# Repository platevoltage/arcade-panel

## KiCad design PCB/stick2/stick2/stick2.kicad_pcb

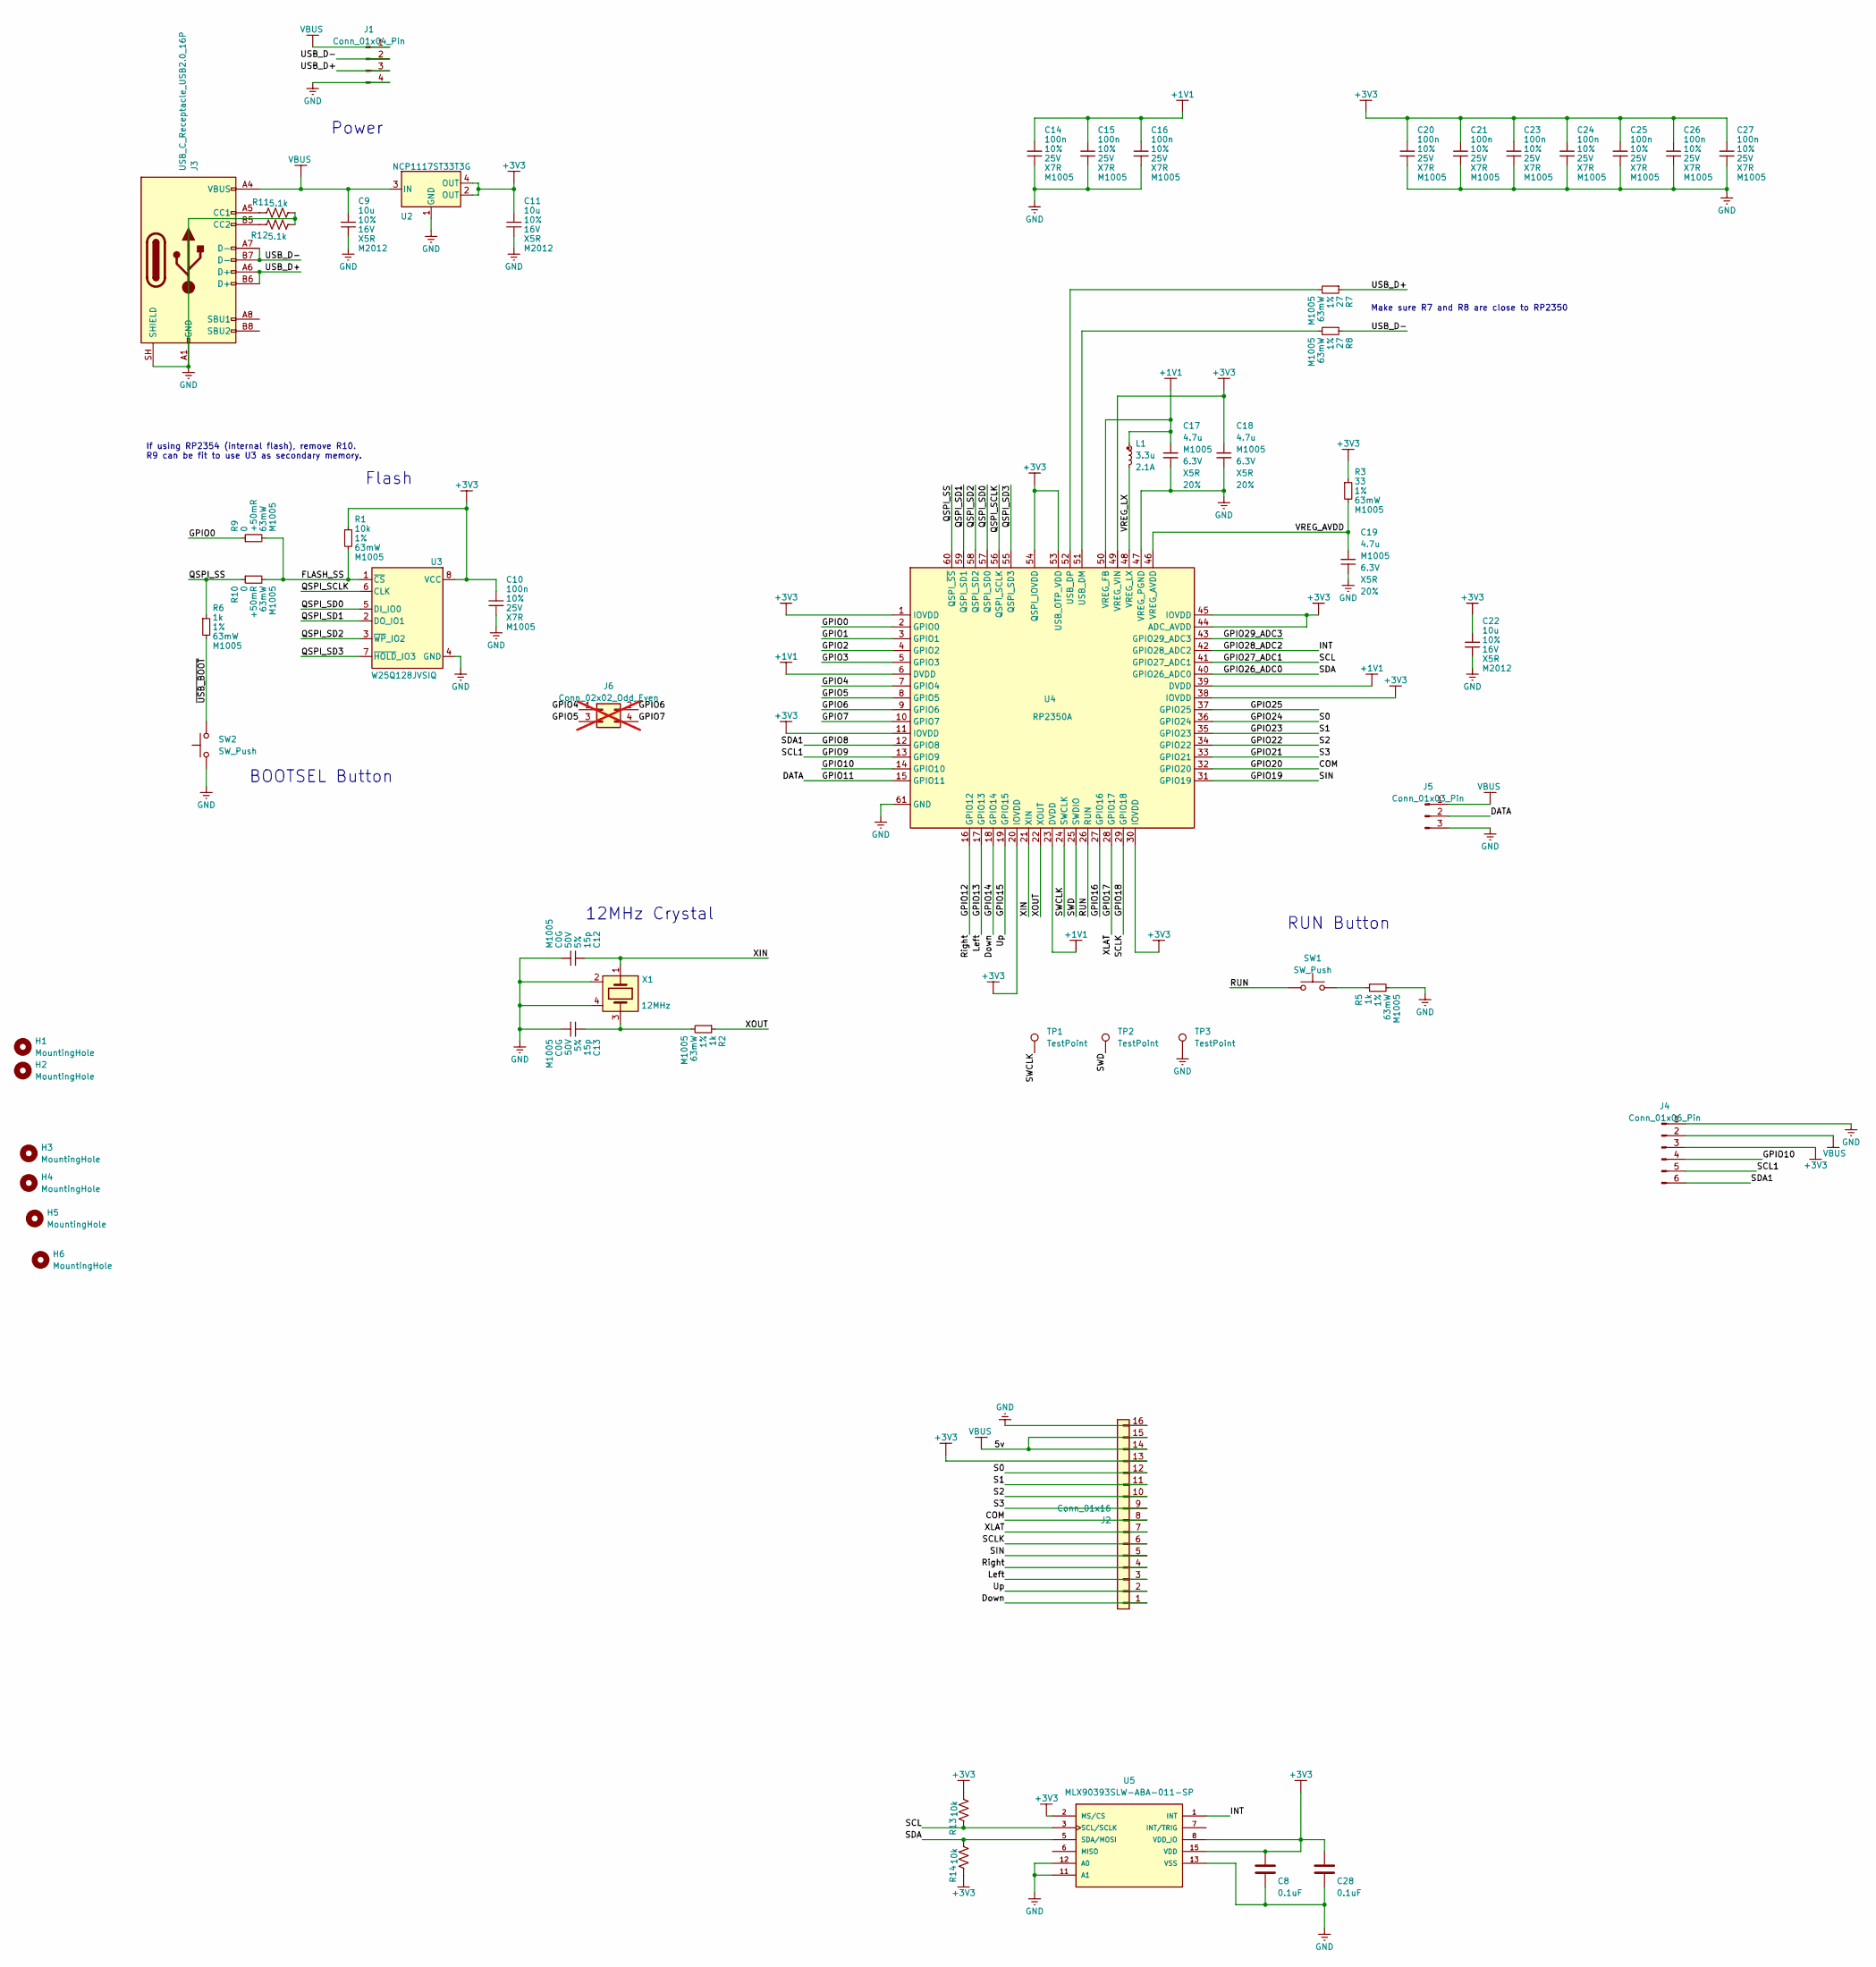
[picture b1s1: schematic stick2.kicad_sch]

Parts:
C8, C28: 0.1uF; C_0603_1608Metric_Pad1.08x0.95mm_HandSolder; LCSC C1525
C9, C11, C22: 10u; generic_capc2012x125; voltage 16V; tolerance 10%; part_uid RP-01GYSK-AVBE41; lcsc_pn C77075
C10, C14, C15, C16, C20, C21, C23, C24, C25, C26, C27: 100n; C_0603_1608Metric_Pad1.08x0.95mm_HandSolder; voltage 25V; tolerance 10%; part_uid RP-01BJ9Y-KRGF41; lcsc_pn C77014
C12, C13: 15p; C_0603_1608Metric_Pad1.08x0.95mm_HandSolder; voltage 50V; tolerance 5%; part_uid RP-01C89W-LLY9XV; lcsc_pn C77014
C17, C18: 4.7u; C_0603_1608Metric_Pad1.08x0.95mm_HandSolder; voltage 6.3V; tolerance 20%; part_uid RP-019A1P-0C2GHY; lcsc_pn C82453
C19: 4.7u; C_0603_1608Metric_Pad1.08x0.95mm_HandSolder; voltage 6.3V; tolerance 20%; part_uid RP-019A1P-0C2GHY; lcsc_pn C77014
H1, H2: MountingHole; MountingHole_6mm
H3, H4, H5, H6: MountingHole; MountingHole_2.2mm_M2
J1: Conn_01x04_Pin; PinHeader_1x04_P2.54mm_Horizontal
J2: Conn_01x16; PinSocket_1x16_P2.54mm_Horizontal
J3: USB_C_Receptacle_USB2.0_16P; USB_C_Receptacle_GCT_USB4110
J4: Conn_01x06_Pin; PinHeader_1x06_P2.54mm_Horizontal
J5: Conn_01x03_Pin; PinHeader_1x03_P2.54mm_Horizontal
J6: Conn_02x02_Odd_Even; PinHeader_2x02_P2.54mm_Vertical; not fitted
L1: 3.3u; abracon_aota-b201610s3r3-101-t; tolerance 20%; part_uid RP-01GY5D-2VC7WP; lcsc_pn C42411119
R1: 10k; R_0603_1608Metric_Pad0.98x0.95mm_HandSolder; tolerance 1%; voltage 50V; part_uid RP-019A1P-53DHSX; lcsc_pn C60490
R2, R5, R6: 1k; R_0603_1608Metric_Pad0.98x0.95mm_HandSolder; tolerance 1%; voltage 50V; part_uid RP-019A1P-4Z6ZWY; lcsc_pn C60490
R3: 33; R_0603_1608Metric_Pad0.98x0.95mm_HandSolder; tolerance 1%; voltage 50V; part_uid RP-019A1P-58PW9L; lcsc_pn C60490
R7, R8: 27; R_0603_1608Metric_Pad0.98x0.95mm_HandSolder; tolerance 1%; voltage 50V; part_uid RP-01C89V-LTEYC4; lcsc_pn C60490
R9, R10: 0; R_0603_1608Metric_Pad0.98x0.95mm_HandSolder; tolerance +50mR; voltage 50V; part_uid RP-019A1P-4Y4V63; lcsc_pn C60490
R11, R12: 5.1k; R_0603_1608Metric_Pad0.98x0.95mm_HandSolder; MFR.Part # RC0603JR-075K1L; JLCPCB Part # C14677
R13, R14: 10k; R_0603_1608Metric_Pad0.98x0.95mm_HandSolder; MFR.Part # RC0603JR-075K1L; JLCPCB Part # C14677
SW1, SW2: SW_Push; SW_SPST_B3U-3000P; Manufacturer Part Numbe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 PTS636 SKG25J SMTR LFS; JLCPCB Part # C2689642
TP1, TP2, TP3: TestPoint; TestPoint_Pad_D2.0mm
U2: NCP1117ST33T3G; onsemi_ncp1117st33t3g; voltage 3.3V; part_uid RP-01JWD9-7JRX6J; lcsc_pn C26537
U3: W25Q128JVSIQ; generic_soic127p790x195-8; voltage 2.7-3.6V; part_uid RP-01JWD4-F1H4N9; lcsc_pn C97521
U4: RP2350A; rpi_rp2350a_vias; part_uid RP-01HA9H-9K5E8T; lcsc_pn C42411118
U5: MLX90393SLW-ABA-011-SP; QFN50P300X300X100-17N; PARTREV 010; LCSC C5371633
X1: 12MHz; generic_xtalcc320x250x80-4; tolerance 30ppm; part_uid RP-01G8X7-GS352B; lcsc_pn C20625731

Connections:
+1V1: C14.1, C15.1, C16.1, C17.1, L1.1, U4.6 (DVDD), U4.23 (DVDD), U4.39 (DVDD), U4.50 (VREG_FB)
+3V3: C8.1, C10.1, C11.1, C18.1, C20.1, C21.1, C22.1, C23.1, C24.1, C25.1, C26.1, C27.1, C28.1, J2.13, J4.3, R1.1, R3.1, R13.2, R14.1, U2.2 (OUT), U2.4 (OUT), U3.8 (VCC), U4.1 (IOVDD), U4.11 (IOVDD), U4.20 (IOVDD), U4.30 (IOVDD), U4.38 (IOVDD), U4.44 (ADC_AVDD), U4.45 (IOVDD), U4.49 (VREG_VIN), U4.53 (USB_OTP_VDD), U4.54 (QSPI_IOVDD), U5.2 (MS/CS), U5.8 (VDD_IO), U5.15 (VDD)
/COM: J2.8, U4.32 (GPIO20)
/DATA: J5.2, U4.15 (GPIO11)
/Down: J2.1, U4.18 (GPIO14)
/FLASH_SS: R1.2, R9.2, R10.2, U3.1 (~CS)
/GPIO0: R9.1, U4.2 (GPIO0)
/GPIO1: U4.3 (GPIO1)
/GPIO2: U4.4 (GPIO2)
/GPIO3: U4.5 (GPIO3)
/GPIO4: J6.1, U4.7 (GPIO4)
/GPIO5: J6.3, U4.8 (GPIO5)
/GPIO6: J6.2, U4.9 (GPIO6)
/GPIO7: J6.4, U4.10 (GPIO7)
/GPIO8: J4.6, U4.12 (GPIO8)
/GPIO9: J4.5, U4.13 (GPIO9)
/GPIO10: J4.4, U4.14 (GPIO10)
/GPIO12: J2.4, U4.16 (GPIO12)
/GPIO13: J2.3, U4.17 (GPIO13)
/GPIO15: J2.2, U4.19 (GPIO15)
/GPIO16: U4.27 (GPIO16)
/GPIO17: J2.7, U4.28 (GPIO17)
/GPIO18: J2.6, U4.29 (GPIO18)
/GPIO19: J2.5, U4.31 (GPIO19)
/GPIO21: J2.9, U4.33 (GPIO21)
/GPIO22: J2.10, U4.34 (GPIO22)
/GPIO23: J2.11, U4.35 (GPIO23)
/GPIO24: J2.12, U4.36 (GPIO24)
/GPIO25: U4.37 (GPIO25)
/GPIO26_ADC0: R14.2, U4.40 (GPIO26_ADC0), U5.5 (SDA/MOSI)
/GPIO27_ADC1: R13.1, U4.41 (GPIO27_ADC1), U5.3 (SCL/SCLK)
/GPIO28_ADC2: U4.42 (GPIO28_ADC2), U5.1 (INT)
/GPIO29_ADC3: U4.43 (GPIO29_ADC3)
/QSPI_SCLK: U3.6 (CLK), U4.56 (QSPI_SCLK)
/QSPI_SD0: U3.5 (DI_IO0), U4.57 (QSPI_SD0)
/QSPI_SD1: U3.2 (DO_IO1), U4.59 (QSPI_SD1)
/QSPI_SD2: U3.3 (~WP_IO2), U4.58 (QSPI_SD2)
/QSPI_SD3: U3.7 (~HOLD_IO3), U4.55 (QSPI_SD3)
/QSPI_SS: R6.1, R10.1, U4.60 (QSPI_~SS)
/RUN: SW1.1, U4.26 (RUN)
/SWCLK: TP1.1 (1_1), U4.24 (SWCLK)
/SWD: TP2.1 (1_1), U4.25 (SWDIO)
/USB_D+: J1.3, J3.A6 (D+), J3.B6 (D+), R7.1
/USB_D-: J1.2, J3.A7 (D-), J3.B7 (D-), R8.1
/VREG_AVDD: C19.1, R3.2, U4.46 (VREG_AVDD)
/VREG_LX: L1.2, U4.48 (VREG_LX)
/XIN: C12.1, U4.21 (XIN), X1.1
/XOUT: R2.1, U4.22 (XOUT)
/~USB_BOOT: R6.2, SW2.2
unnamed: C13.1, R2.2, X1.3
unnamed: J3.A5 (CC1), R11.1
unnamed: J3.B5 (CC2), R12.1
unnamed: R5.1, SW1.2
unnamed: R8.2, U4.51 (USB_DM)
unnamed: R7.2, U4.52 (USB_DP)
VBUS: C9.1, J1.1, J2.14, J2.15, J3.A4 (VBUS), J3.A9 (VBUS), J3.B4 (VBUS), J3.B9 (VBUS), J4.2, J5.1, U2.3 (IN)

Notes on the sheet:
Make sure R7 and R8 are close to RP2350
12MHz Crystal
Power
BOOTSEL Button
If using RP2354 (internal flash), remove R10. R9 can be fit to use U3 as secondary memory.
RUN Button
Flash

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
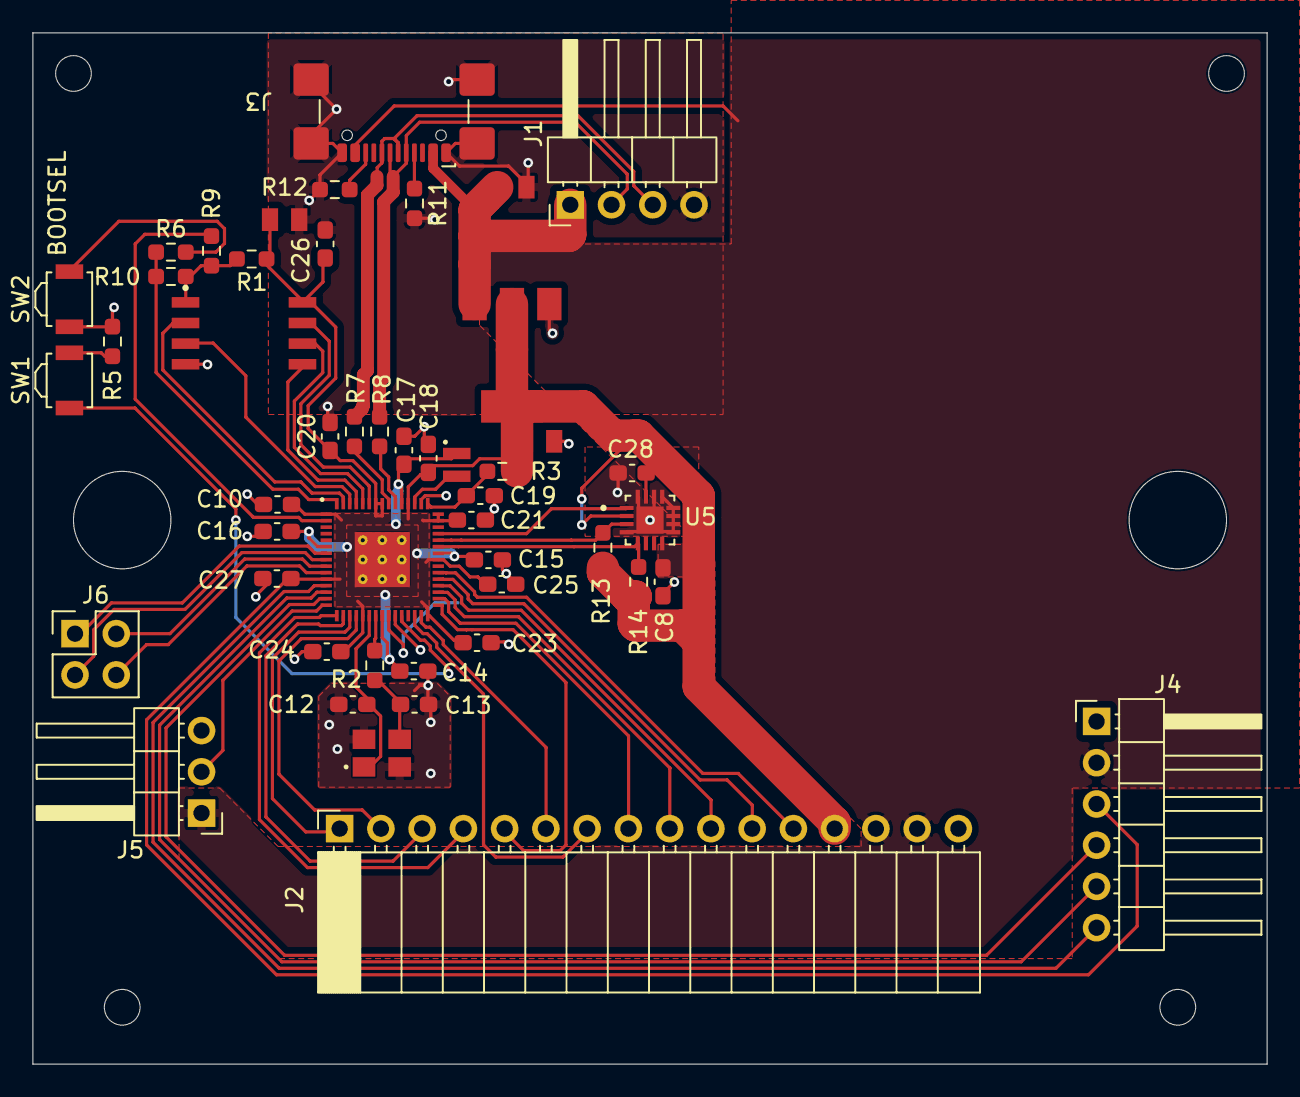
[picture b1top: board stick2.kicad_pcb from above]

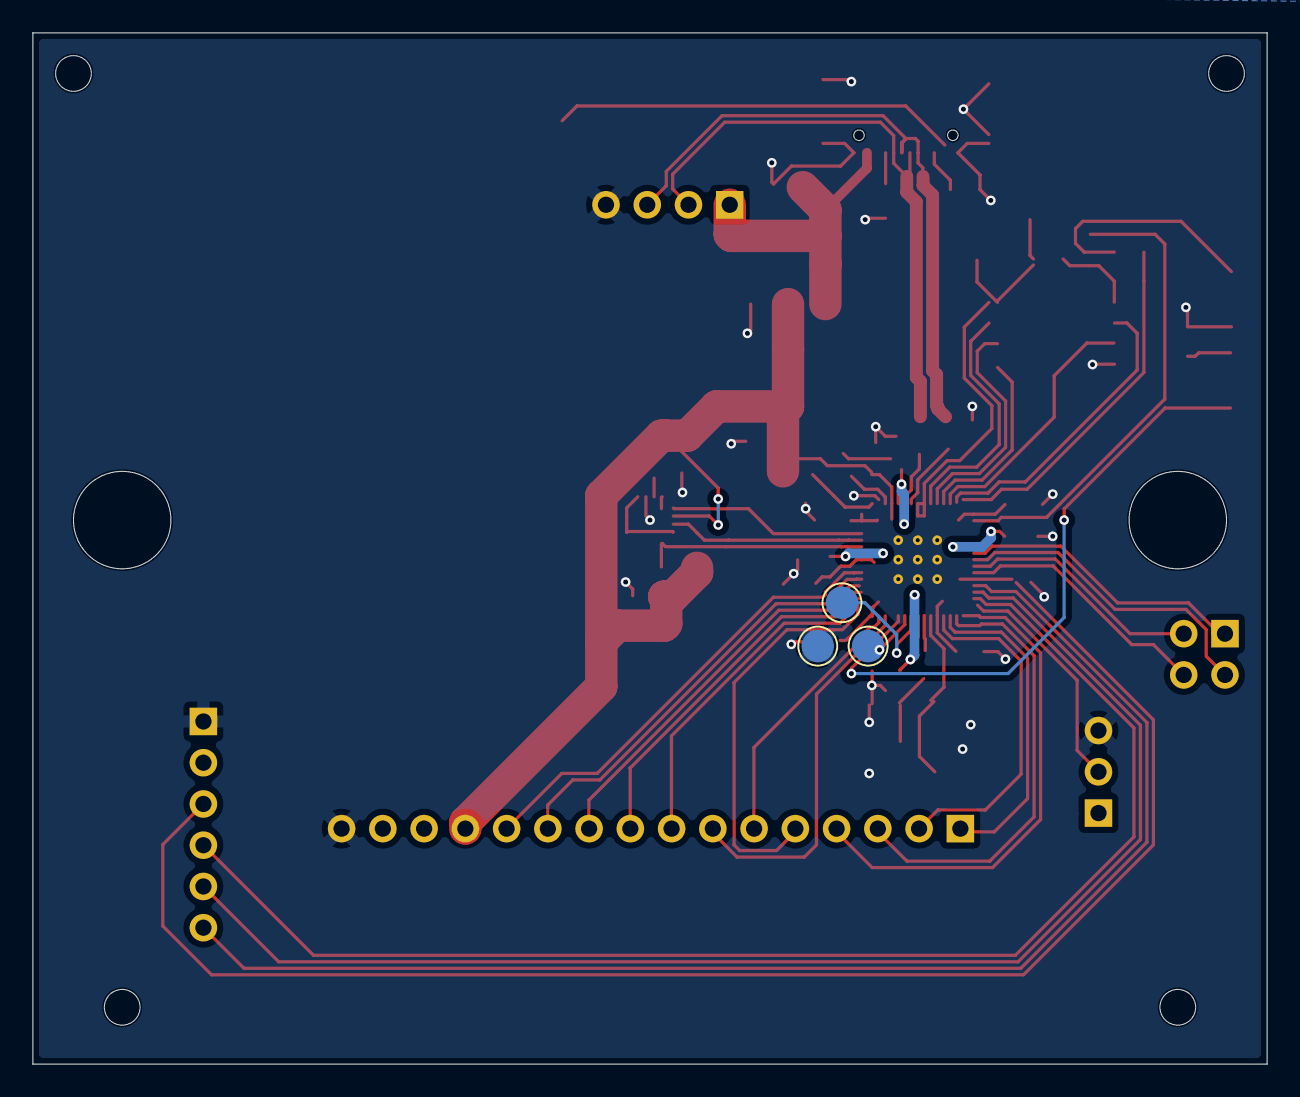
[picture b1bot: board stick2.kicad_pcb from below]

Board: 2 copper layers, 76.0 x 63.5 mm, 57 parts (3 on the bottom side), 51 nets.

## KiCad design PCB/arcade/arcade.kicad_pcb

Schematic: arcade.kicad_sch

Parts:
C1, C2: 10uf; C_0603_1608Metric_Pad1.08x0.95mm_HandSolder; MFR.Part # CC0603MRX5R5BB106; JLCPCB Part # C109454
C6: 100nf; C_0603_1608Metric_Pad1.08x0.95mm_HandSolder; MFR.Part # CC0603KRX7R0BB104; JLCPCB Part # C113803
C15, C17, C18, C19, C20, C21, C22, C23, C24: 100nf; C_0603_1608Metric_Pad1.08x0.95mm_HandSolder; MFR.Part # CC0603JRNPO9BN220; JLCPCB Part # C105620
C16: 2.2uf; C_0603_1608Metric_Pad1.08x0.95mm_HandSolder; MFR.Part # CC0603JRNPO9BN220; JLCPCB Part # C105620
D1: SK6812MINI-E; LED_SK6812MINI_PLCC4_3.5x3.5mm_P1.75mm
H1, H2, H3, H4: MountingHole; MountingHole_2.5mm_Pad_TopBottom
J1: USB_C_Receptacle_USB2.0_16P; USB_C_Receptacle_GCT_USB4110
J2: Conn_02x03_Odd_Even; PinHeader_2x03_P2.54mm_Horizontal
J3: Conn_02x06_Odd_Even; PinHeader_2x06_P2.54mm_Horizontal
J4: Screw_Terminal_01x02; TerminalBlock_Phoenix_MKDS-3-2-5.08_1x02_P5.08mm_Horizontal
J5, J7: Screw_Terminal_01x12; TerminalBlock_Phoenix_MPT-0,5-12-2.54_1x12_P2.54mm_Horizont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
J6: Screw_Terminal_01x08; TerminalBlock_Phoenix_MPT-0,5-8-2.54_1x08_P2.54mm_Horizontal
J8: Conn_01x02_Pin; PinHeader_1x02_P2.54mm_Vertical
J9: Conn_01x06_Pin; PinHeader_1x06_P2.54mm_Vertical
J10: USB3_A_Stacked; USB3_A_Molex_48406-0001_Horizontal_Stacked
J11: USB_A_Stacked; USB_A_CUI_UJ2-ADH-TH_Horizontal_Stacked
J13: HDMI_A_1.4; HDMI_A_Amphenol_10029449-x01xLF_Horizontal
J15, J16: Conn_02x24_Odd_Even; PinHeader_2x24_P2.54mm_Horizontal
Module1: ComputeModule5-CM5; Raspberry-Pi-5-Compute-Module
R4, R5, R10: 5.1k; R_0603_1608Metric_Pad0.98x0.95mm_HandSolder; MFR.Part # RC0603JR-075K1L; JLCPCB Part # C14677
R11, R12: 27; R_0603_1608Metric_Pad0.98x0.95mm_HandSolder; MFR.Part # RC0603JR-075K1L; JLCPCB Part # C14677
U1: RP2040; QFN-56-1EP_7x7mm_P0.4mm_EP3.2x3.2mm
U2, U3, U4: TLC5947RHB; QFN-32-1EP_5x5mm_P0.5mm_EP3.45x3.45mm
U5: ME6211C33M5; SOT-23-5; MFR.Part # ME6211C33M5G-N; JLCPCB Part # C82942
U6, U7: CD74HC4067M; SSOP-24_5.3x8.2mm_P0.65mm
U8: W25Q16JVSS; SOIC-8_5.3x5.3mm_P1.27mm
U9: TS3USB221ARSERG4; RSE10
U10: TCA9548AMRGER; Texas_RGE0024C_VQFN-24-1EP_4x4mm_P0.5mm_EP2.1x2.1mm
Y3: Crystal_GND24; Crystal_SMD_2520-4Pin_2.5x2.0mm; MFR.Part # XYDBPCNANF-12MHZ; JLCPCB Part # C521567

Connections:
/3.3v: C2.1, C6.1, C15.1, C16.1, C17.2, C18.2, C19.2, C20.2, C21.2, C22.2, J3.9, J3.10, U1.1 (IOVDD), U1.10 (IOVDD), U1.22 (IOVDD), U1.33 (IOVDD), U1.42 (IOVDD), U1.49 (IOVDD), U5.5 (V_{OUT}), U6.24 (VCC), U7.24 (VCC), U8.8 (VCC)
/CS1: J3.1
/CS2: J3.2
/D1+: R12.2
/D1-: R11.2
/DU+: J1.A6 (D+), J1.B6 (D+)
/DU-: J1.A7 (D-), J1.B7 (D-)
/EXT_5V: J2.5, J2.6, J4.2, J8.1, J15.7, J15.8, J15.15, J15.16, J15.23, J15.24, J15.31, J15.32, J15.39, J15.40, J15.47, J15.48, J16.7, J16.8, J16.15, J16.16, J16.23, J16.24, J16.31, J16.32, J16.39, J16.40, J16.47, J16.48, U2.28 (VCC), U3.28 (VCC), U4.28 (VCC)
/GND: C1.2, C2.2, C6.2, C15.2, C16.2, C17.1, C18.1, C19.1, C20.1, C21.1, C22.1, C23.1, C24.2, D1.3 (VDD), J1.A1 (GND), J1.A12 (GND), J1.B1 (GND), J1.B12 (GND), J1.S1 (SHIELD), J2.1, J2.2, J3.11, J3.12, J4.1, J9.6, R4.2, R5.2, U1.57 (GND), U2.29 (GND), U2.33 (PowerPAD), U3.29 (GND), U3.33 (PowerPAD), U4.29 (GND), U4.33 (PowerPAD), U5.2 (V_{SS}), U6.12 (GND), U7.12 (GND), U8.4 (GND), Y3.2, Y3.4
/IO14: D1.2 (DIN)
/IO38: J2.4
/IO40: U2.26 (XLAT), U3.26 (XLAT), U4.26 (XLAT)
/IO41: U2.31 (SCLK), U3.31 (SCLK), U4.31 (SCLK)
/IO42: U2.32 (SIN)
/MISO: J3.3, J3.4
/MOSI: J3.5, J3.6
/PD0: U6.10 (S0), U7.10 (S0)
/PD1: U6.11 (S1), U7.11 (S1)
/PD4: U6.14 (S2), U7.14 (S2)
/PD5: U6.15 (~E)
/PD6: U6.13 (S3), U7.13 (S3)
/PD7: U7.15 (~E)
/QSPI_SCLK: U1.52 (QSPI_SCLK), U8.6 (CLK)
/QSPI_SD0: U1.53 (QSPI_SD0), U8.5 (DI/IO_{0})
/QSPI_SD1: U1.55 (QSPI_SD1), U8.2 (DO/IO_{1})
/QSPI_SD2: U1.54 (QSPI_SD2), U8.3 (~WP/IO_{2})
/QSPI_SD3: U1.51 (QSPI_SD3), U8.7 (~HOLD/~RESET/IO_{3})
/QSPI_SS: U1.56 (~QSPI_SS), U8.1 (~CS)
/RX0: J9.2, U1.17 (GPIO14)
/SCK: J3.7, J3.8
/TX0: J9.3, U1.16 (GPIO13)
/VBUS: C1.1, D1.1 (VSS), J1.A4 (VBUS), J1.A9 (VBUS), J1.B4 (VBUS), J1.B9 (VBUS), J8.2, J9.4, U5.1 (V_{IN}), U5.3 (CE)
/XIN: C24.1, U1.20 (XIN), Y3.1
/XOUT: R10.2, U1.21 (XOUT)
unnamed: C23.2, R10.1, Y3.3
unnamed: J1.A5 (CC1), R4.1
unnamed: J1.B5 (CC2), R5.1
unnamed: J5.1, U6.20 (I11)
unnamed: J5.2, U6.21 (I10)
unnamed: J5.3, U6.22 (I9)
unnamed: J5.4, U6.23 (I8)
unnamed: J5.5, U6.2 (I7)
unnamed: J5.6, U6.3 (I6)
unnamed: J5.7, U6.4 (I5)
unnamed: J5.8, U6.5 (I4)
unnamed: J5.9, U6.6 (I3)
unnamed: J5.10, U6.7 (I2)
unnamed: J5.11, U6.8 (I1)
unnamed: J5.12, U6.9 (I0)
unnamed: J6.1, U6.19 (I12)
unnamed: J6.2, U6.18 (I13)
unnamed: J6.3, U6.17 (I14)
unnamed: J6.4, U6.16 (I15)
unnamed: J6.5, U7.9 (I0)
unnamed: J6.6, U7.8 (I1)
unnamed: J6.7, U7.7 (I2)
unnamed: J6.8, U7.6 (I3)
unnamed: J7.1, U7.5 (I4)
unnamed: J7.2, U7.4 (I5)
unnamed: J7.3, U7.3 (I6)
unnamed: J7.4, U7.2 (I7)
unnamed: J7.5, U7.23 (I8)
unnamed: J7.6, U7.22 (I9)
unnamed: J7.7, U7.21 (I10)
unnamed: J7.8, U7.20 (I11)
unnamed: J7.9, U7.19 (I12)
unnamed: J7.10, U7.18 (I13)
unnamed: J7.11, U7.17 (I14)
unnamed: J7.12, U7.16 (I15)
unnamed: J15.1, U2.24 (OUT23)
unnamed: J15.2, U3.13 (OUT12)
unnamed: J15.3, U2.23 (OUT22)
unnamed: J15.4, U3.14 (OUT13)
unnamed: J15.5, U2.22 (OUT21)
unnamed: J15.6, U3.15 (OUT14)
unnamed: J15.9, U2.21 (OUT20)
unnamed: J15.10, U3.16 (OUT15)
unnamed: J15.11, U2.20 (OUT19)
unnamed: J15.12, U3.17 (OUT16)
unnamed: J15.13, U2.19 (OUT18)
unnamed: J15.14, U3.18 (OUT17)
unnamed: J15.17, U2.18 (OUT17)
unnamed: J15.18, U3.19 (OUT18)
unnamed: J15.19, U2.17 (OUT16)
unnamed: J15.20, U3.20 (OUT19)
unnamed: J15.21, U2.16 (OUT15)
unnamed: J15.22, U3.21 (OUT20)
unnamed: J15.25, U2.15 (OUT14)
unnamed: J15.26, U3.22 (OUT21)
unnamed: J15.27, U2.14 (OUT13)
unnamed: J15.28, U3.23 (OUT22)
unnamed: J15.29, U2.13 (OUT12)
unnamed: J15.30, U3.24 (OUT23)
unnamed: J15.33, U2.12 (OUT11)
unnamed: J15.34, U2.1 (OUT0)
unnamed: J15.35, U2.11 (OUT10)
unnamed: J15.36, U2.2 (OUT1)
unnamed: J15.37, U2.10 (OUT9)
unnamed: J15.38, U2.3 (OUT2)
unnamed: J15.41, U2.9 (OUT8)
unnamed: J15.42, U2.4 (OUT3)
unnamed: J15.43, U2.8 (OUT7)
unnamed: J15.44, U2.5 (OUT4)
unnamed: J15.45, U2.7 (OUT6)
unnamed: J15.46, U2.6 (OUT5)
unnamed: J16.1, U4.18 (OUT17)
unnamed: J16.2, U4.19 (OUT18)
unnamed: J16.3, U4.17 (OUT16)
unnamed: J16.4, U4.20 (OUT19)
unnamed: J16.5, U4.16 (OUT15)
unnamed: J16.6, U4.21 (OUT20)
unnamed: J16.9, U4.15 (OUT14)
unnamed: J16.10, U4.22 (OUT21)
unnamed: J16.11, U4.14 (OUT13)
unnamed: J16.12, U4.23 (OUT22)
unnamed: J16.13, U4.13 (OUT12)
unnamed: J16.14, U4.24 (OUT23)
unnamed: J16.17, U4.12 (OUT11)
unnamed: J16.18, U3.1 (OUT0)
unnamed: J16.19, U4.11 (OUT10)
unnamed: J16.20, U3.2 (OUT1)
unnamed: J16.21, U4.10 (OUT9)
unnamed: J16.22, U3.3 (OUT2)
unnamed: J16.25, U4.9 (OUT8)
unnamed: J16.26, U3.4 (OUT3)
unnamed: J16.27, U4.8 (OUT7)
unnamed: J16.28, U3.5 (OUT4)
unnamed: J16.29, U4.7 (OUT6)
unnamed: J16.30, U3.6 (OUT5)
unnamed: J16.33, U4.6 (OUT5)
unnamed: J16.34, U3.7 (OUT6)
unnamed: J16.35, U4.5 (OUT4)
unnamed: J16.36, U3.8 (OUT7)
unnamed: J16.37, U4.4 (OUT3)
unnamed: J16.38, U3.9 (OUT8)
unnamed: J16.41, U4.3 (OUT2)
unnamed: J16.42, U3.10 (OUT9)
unnamed: J16.43, U4.2 (OUT1)
unnamed: J16.44, U3.11 (OUT10)
unnamed: J16.45, U4.1 (OUT0)
unnamed: J16.46, U3.12 (OUT11)
unnamed: U1.23 (DVDD), U1.50 (DVDD)
unnamed: R11.1, U1.46 (USB_DM)
unnamed: R12.1, U1.47 (USB_DP)
unnamed: U2.25 (SOUT), U3.32 (SIN)
unnamed: U3.25 (SOUT), U4.32 (SIN)

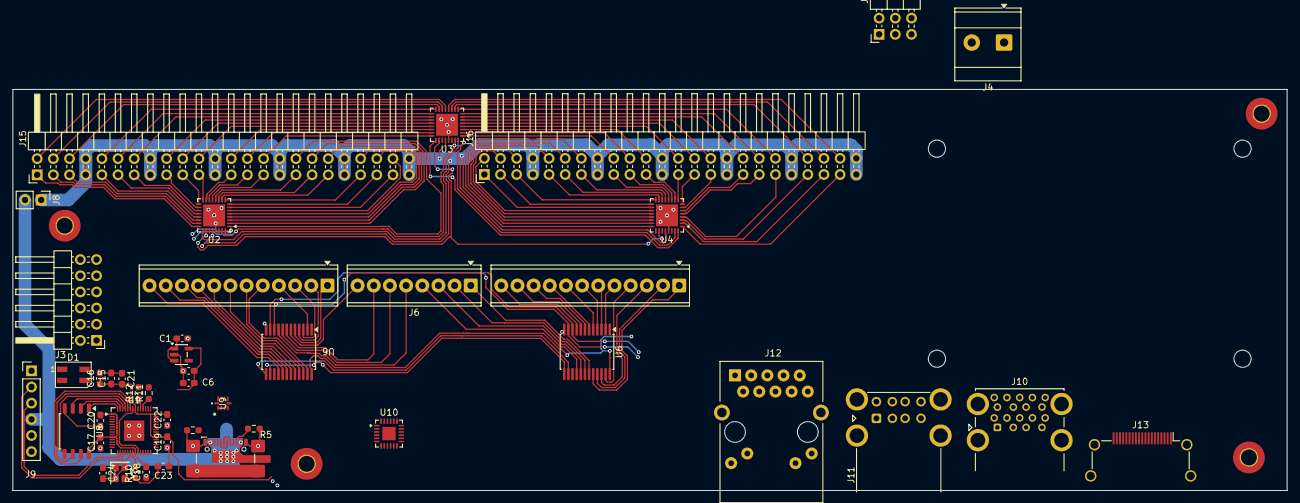
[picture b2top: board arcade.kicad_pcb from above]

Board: 4 copper layers, 200.1 x 63.0 mm, 50 parts (1 on the bottom side), 137 nets.

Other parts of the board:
J12: RJ45_RB1-125B8G1A; RJ45_UDE_RB1-125B8G1A

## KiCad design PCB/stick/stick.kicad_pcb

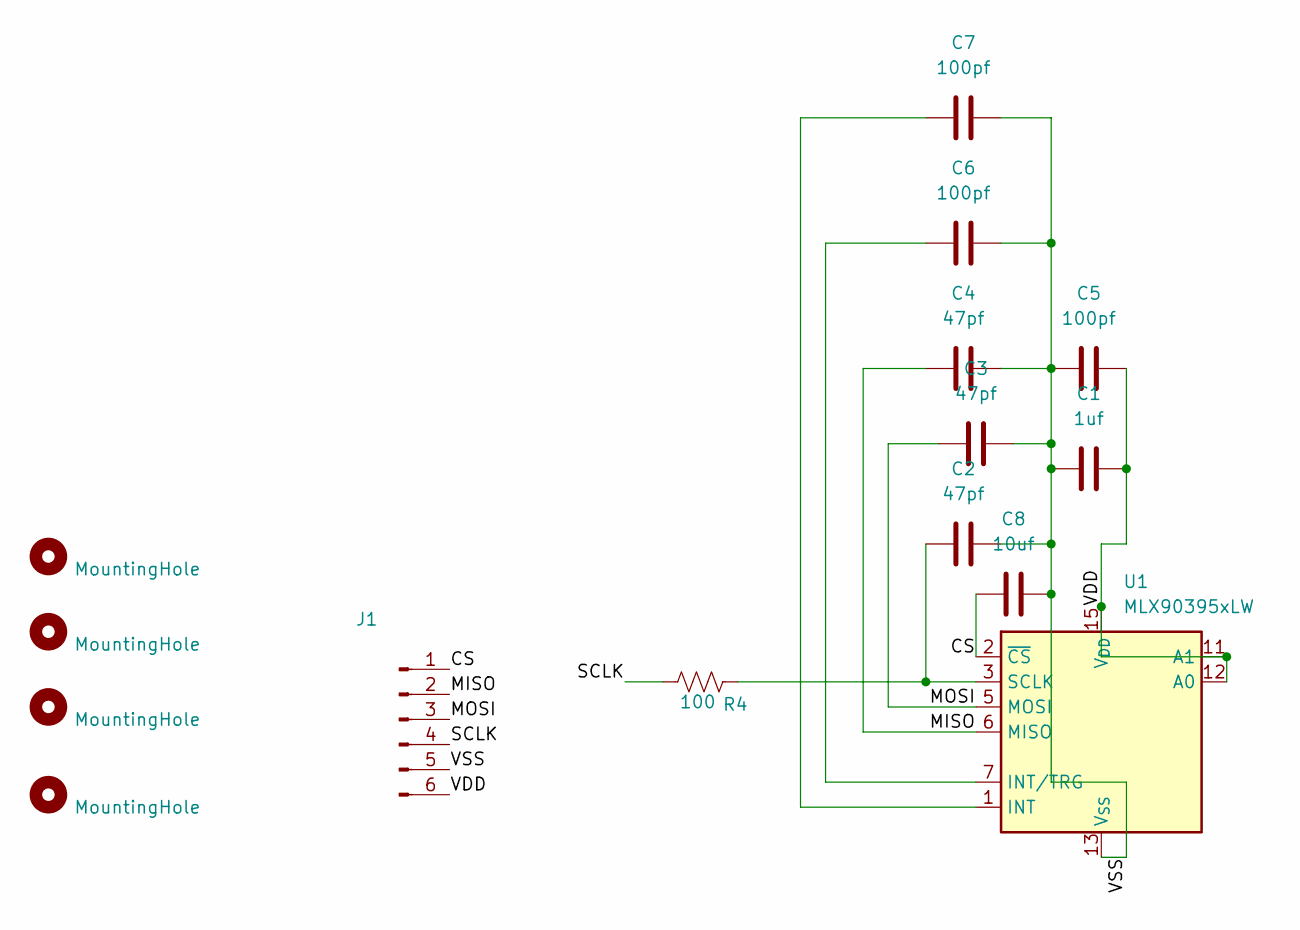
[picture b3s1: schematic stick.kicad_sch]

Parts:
C1: 1uf; C_0603_1608Metric_Pad1.08x0.95mm_HandSolder; MFR.Part # CC0603MRX5R5BB106; JLCPCB Part # C109454
C2, C3, C4: 47pf; C_0603_1608Metric_Pad1.08x0.95mm_HandSolder; MFR.Part # CC0603MRX5R5BB106; JLCPCB Part # C109454
C5, C6, C7: 100pf; C_0603_1608Metric_Pad1.08x0.95mm_HandSolder; MFR.Part # CC0603MRX5R5BB106; JLCPCB Part # C109454
C8: 10uf; C_0603_1608Metric_Pad1.08x0.95mm_HandSolder; MFR.Part # CC0603MRX5R5BB106; JLCPCB Part # C109454
H1, H2, H3, H4: MountingHole; MountingHole_3.2mm_M3
J1: Conn_01x06_Pin; PinHeader_1x06_P2.54mm_Horizontal
R4: 100; R_0603_1608Metric_Pad0.98x0.95mm_HandSolder; MFR.Part # RC0603JR-075K1L; JLCPCB Part # C14677
U1: MLX90395xLW; QFN-16-1EP_3x3mm_P0.5mm_EP1.675x1.675mm

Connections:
/CS: C8.1, J1.1, U1.2 (~CS)
/MISO: C4.1, J1.2, U1.6 (MISO)
/MOSI: C3.1, J1.3, U1.5 (MOSI)
/SCLK: J1.4, R4.2
/VDD: C1.2, C5.1, J1.6, U1.11 (A1), U1.12 (A0), U1.15 (V_{DD})
/VSS: C1.1, C2.2, C3.2, C4.2, C5.2, C6.2, C7.2, C8.2, J1.5, U1.4 (V_{SS}), U1.8 (V_{SS}), U1.9 (V_{SS}), U1.10 (V_{SS}), U1.13 (V_{SS}), U1.14 (V_{SS}), U1.16 (V_{SS}), U1.17 (V_{SS})
unnamed: C7.1, U1.1 (INT)
unnamed: C6.1, U1.7 (INT/TRG)
unnamed: C2.1, R4.1, U1.3 (SCLK)

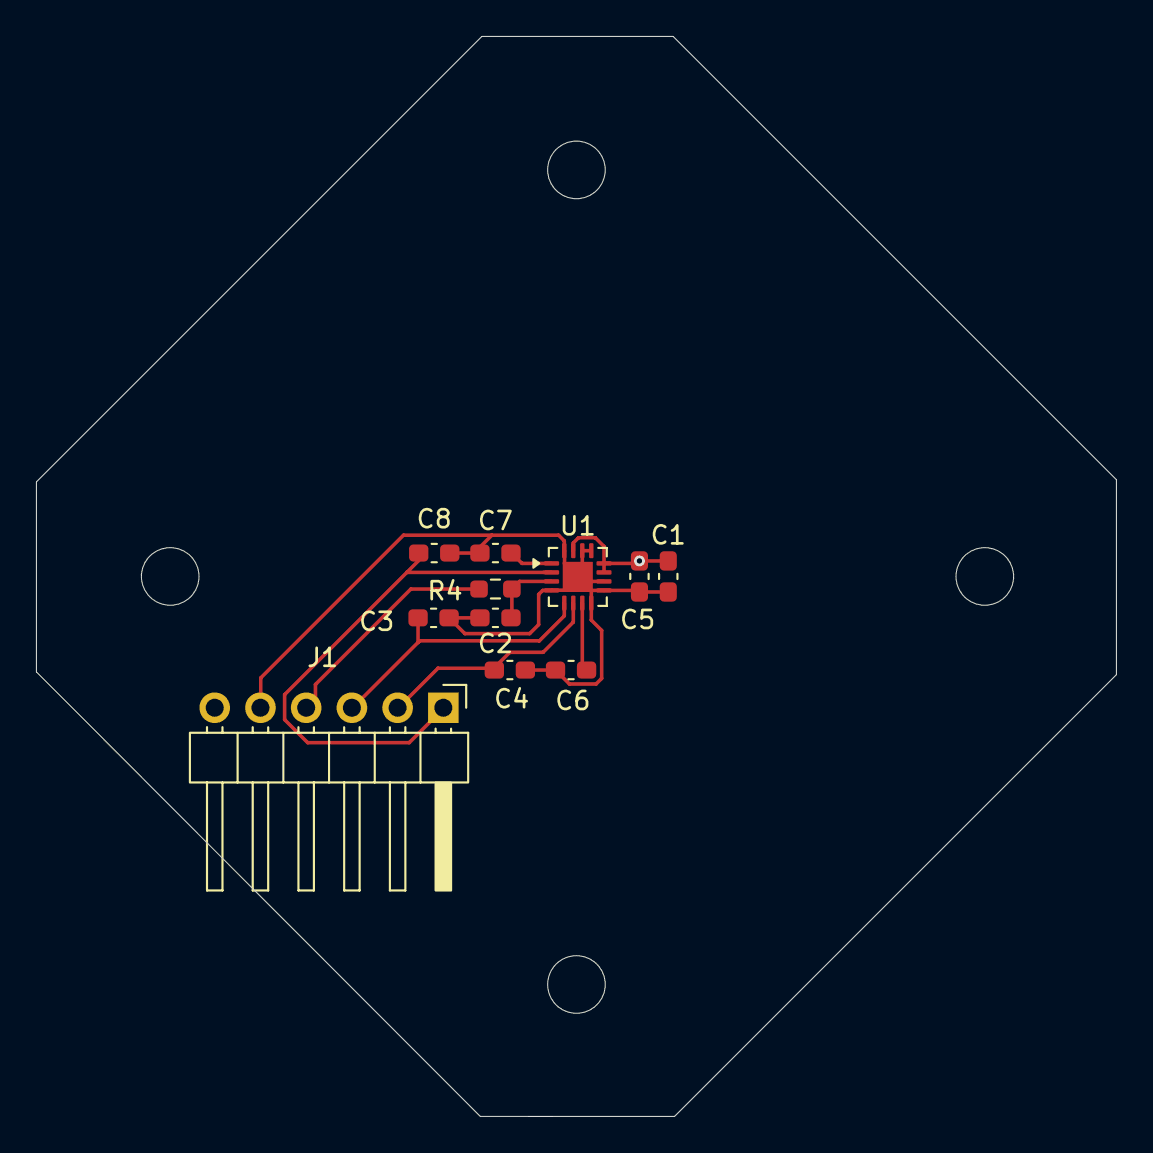
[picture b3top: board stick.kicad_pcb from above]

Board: 2 copper layers, 60.0 x 60.0 mm, 15 parts (0 on the bottom side), 9 nets.

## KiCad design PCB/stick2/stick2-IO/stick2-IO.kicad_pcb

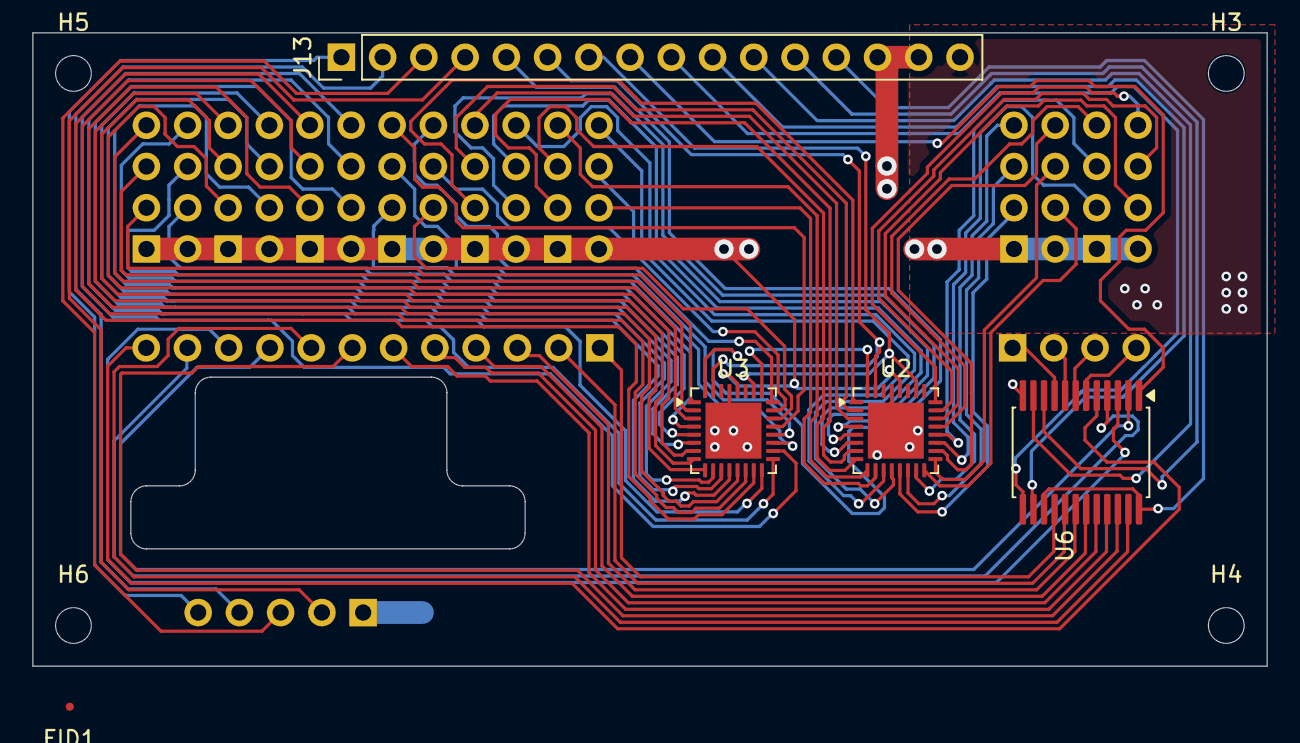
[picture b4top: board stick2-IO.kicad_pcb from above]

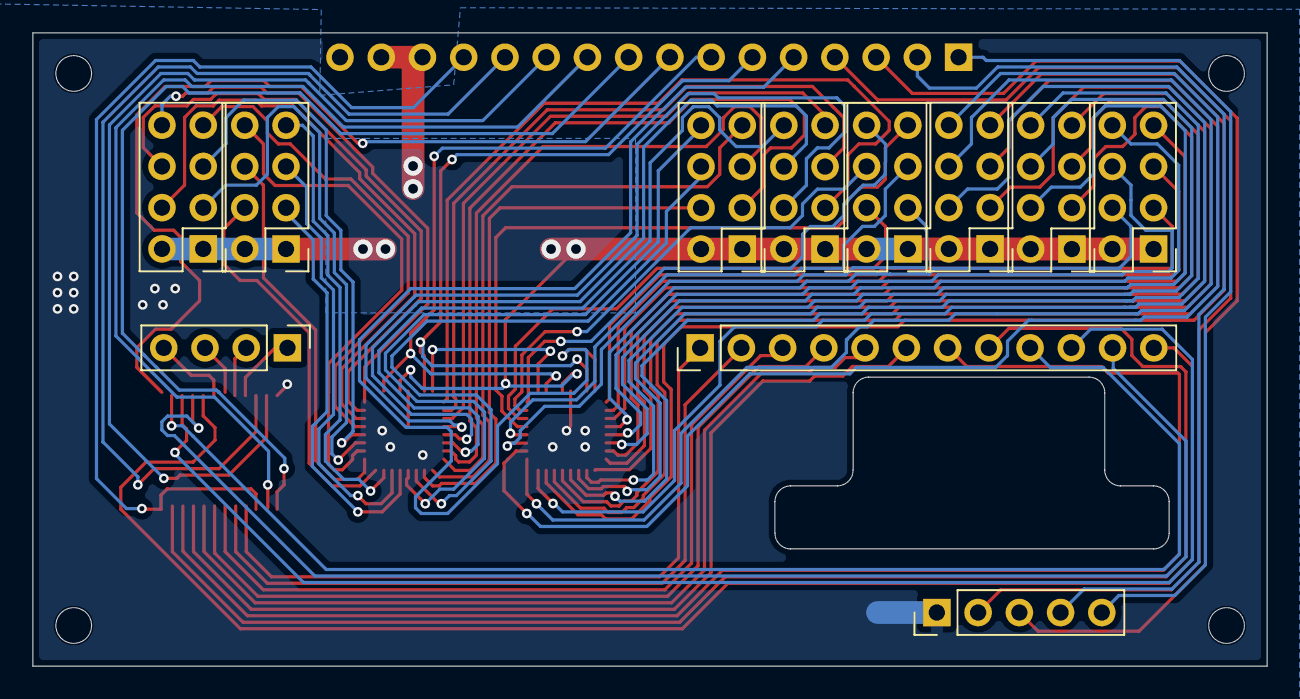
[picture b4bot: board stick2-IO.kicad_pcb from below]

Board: 2 copper layers, 76.0 x 39.0 mm, 20 parts (11 on the bottom side), 80 nets.

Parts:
FID1: Fiducial; Fiducial_0.5mm_Mask1mm
H3, H4, H5, H6: MountingHole; MountingHole_2.2mm_M2
J2, J3, J4, J5, J6, J7, J8, J9: Conn_02x04_Row_Letter_Last; PinHeader_2x04_P2.54mm_Vertical
J10: Conn_01x12_Pin; PinHeader_1x12_P2.54mm_Vertical
J11: Conn_01x04_Pin; PinHeader_1x04_P2.54mm_Vertical
J12: Conn_01x05_Pin; PinHeader_1x05_P2.54mm_Vertical
J13: Conn_01x16_Pin; PinHeader_1x16_P2.54mm_Vertical
U2, U3: TLC5947RHB; QFN-32-1EP_5x5mm_P0.5mm_EP3.45x3.45mm
U6: CD74HC4067M; SSOP-24_5.3x8.2mm_P0.65mm

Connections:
/3.3v: J13.13, U6.15 (~E), U6.24 (VCC)
/5v: J2.1, J2.2, J3.1, J3.2, J4.1, J4.2, J5.1, J5.2, J6.1, J6.2, J7.1, J7.2, J8.1, J8.2, J9.1, J9.2, J13.14, J13.15, U2.28 (VCC), U3.28 (VCC)
/COM: J13.8, U6.1 (COM)
/Down: J12.5, J13.1
/GND: J12.1, J13.16, U2.29 (GND), U2.33 (PowerPAD), U3.29 (GND), U3.33 (PowerPAD), U6.12 (GND)
/Left: J12.3, J13.3
/Right: J12.2, J13.4
/S0: J13.12, U6.10 (S0)
/S1: J13.11, U6.11 (S1)
/S2: J13.10, U6.14 (S2)
/S3: J13.9, U6.13 (S3)
/SCLK: J13.6, U2.31 (SCLK), U3.31 (SCLK)
/SIN: J13.5, U3.32 (SIN)
/Up: J12.4, J13.2
/XLAT: J13.7, U2.26 (XLAT), U3.26 (XLAT)
unnamed: J2.3, U3.1 (OUT0)
unnamed: J2.4, U3.4 (OUT3)
unnamed: J2.5, U3.2 (OUT1)
unnamed: J2.6, U3.5 (OUT4)
unnamed: J2.7, U3.3 (OUT2)
unnamed: J2.8, U3.6 (OUT5)
unnamed: J3.3, U3.7 (OUT6)
unnamed: J3.4, U3.10 (OUT9)
unnamed: J3.5, U3.8 (OUT7)
unnamed: J3.6, U3.11 (OUT10)
unnamed: J3.7, U3.9 (OUT8)
unnamed: J3.8, U3.12 (OUT11)
unnamed: J4.3, U3.13 (OUT12)
unnamed: J4.4, U3.16 (OUT15)
unnamed: J4.5, U3.14 (OUT13)
unnamed: J4.6, U3.17 (OUT16)
unnamed: J4.7, U3.15 (OUT14)
unnamed: J4.8, U3.18 (OUT17)
unnamed: J5.3, U3.19 (OUT18)
unnamed: J5.4, U3.22 (OUT21)
unnamed: J5.5, U3.20 (OUT19)
unnamed: J5.6, U3.23 (OUT22)
unnamed: J5.7, U3.21 (OUT20)
unnamed: J5.8, U3.24 (OUT23)
unnamed: J6.3, U2.1 (OUT0)
unnamed: J6.4, U2.4 (OUT3)
unnamed: J6.5, U2.2 (OUT1)
unnamed: J6.6, U2.5 (OUT4)
unnamed: J6.7, U2.3 (OUT2)
unnamed: J6.8, U2.6 (OUT5)
unnamed: J7.3, U2.7 (OUT6)
unnamed: J7.4, U2.10 (OUT9)
unnamed: J7.5, U2.8 (OUT7)
unnamed: J7.6, U2.11 (OUT10)
unnamed: J7.7, U2.9 (OUT8)
unnamed: J7.8, U2.12 (OUT11)
unnamed: J8.3, U2.13 (OUT12)
unnamed: J8.4, U2.16 (OUT15)
unnamed: J8.5, U2.14 (OUT13)
unnamed: J8.6, U2.17 (OUT16)
unnamed: J8.7, U2.15 (OUT14)
unnamed: J8.8, U2.18 (OUT17)
unnamed: J9.3, U2.19 (OUT18)
unnamed: J9.4, U2.22 (OUT21)
unnamed: J9.5, U2.20 (OUT19)
unnamed: J9.6, U2.23 (OUT22)
unnamed: J9.7, U2.21 (OUT20)
unnamed: J9.8, U2.24 (OUT23)
unnamed: J10.1, U6.16 (I15)
unnamed: J10.2, U6.17 (I14)
unnamed: J10.3, U6.18 (I13)
unnamed: J10.4, U6.19 (I12)
unnamed: J10.5, U6.20 (I11)
unnamed: J10.6, U6.21 (I10)
unnamed: J10.7, U6.22 (I9)
unnamed: J10.8, U6.23 (I8)
unnamed: J10.9, U6.2 (I7)
unnamed: J10.10, U6.3 (I6)
unnamed: J10.11, U6.4 (I5)
unnamed: J10.12, U6.5 (I4)
unnamed: J11.1, U6.9 (I0)
unnamed: J11.2, U6.8 (I1)
unnamed: J11.3, U6.7 (I2)
unnamed: J11.4, U6.6 (I3)
unnamed: U2.32 (SIN), U3.25 (SOUT)
